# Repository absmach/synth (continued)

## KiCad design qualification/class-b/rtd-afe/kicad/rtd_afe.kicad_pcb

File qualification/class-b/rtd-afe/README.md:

# PT100 4-wire RTD analog front end (SYN-363)

Status: design, placement and a FreeRouting route that is **untrusted and not
release-ready**. The committed evidence is historical (source revision
`01a77d54`); on default settings the export ends `validation_failed` with 12
blocking return-via findings. The board is **not fabricated and not tested on
hardware**. The
SI/PI/RF review is being carried out by the designated reviewer; the automated
evidence and the open items are in [QUALIFICATION.md](QUALIFICATION.md). The
analog accuracy has not been measured, and several sourcing and decoupling items
are open (see Known limits and gaps).

Intended use: a bench or lab 4-wire PT100 front end with a USB readout. It is a
compact mixed-signal board on a single ground plane, not an instrument. Do not
use it for a product or a safety function until the review items in
QUALIFICATION.md are closed.

## What it is

- 4-wire PT100 input on J2 (1x4, 2.54 mm): pin 1 F+, pin 2 S+, pin 3 S-, pin 4
  F-. The force pair carries the excitation current; the sense pair reads the
  element.
- Input filter: R_S1/R_S2 1k 0.1 %, C_D 100 nF X7R across the pair, C_CM1/C_CM2
  10 nF C0G to GND, C_F 10 nF C0G on F+.
- U1 TI ADS124S08 24-bit delta-sigma ADC (VQFN-32, exposed pad) with the
  internal PGA and IDAC1. AIN0 is the force output, AIN1/AIN2 the differential
  sense input. The firmware is expected to select 1 mA excitation.
- U3 TI REF5025AIDR 2.5 V reference on REFP0/REFN0. C_RI and C_RV are 1 uF.
- U2 Raspberry Pi RP2350A (QFN-60), U4 W25Q128JVSIQ QSPI flash (SOIC-8 208 mil, registry `w25q128_flash_208mil`), Y1 ECS-120-20-33-TR
  12 MHz crystal with 33 pF C0G load caps, J3 3-pin SWD header, RUN pull-up.
- J1 USB-C receptacle (HRO TYPE-C-31-M-12), 5.1k CC1/CC2, 27R series on D+/D-,
  D1/D2 SOD-323 TVS on D+/D-. U5 TI LP5907-3.3 LDO (250 mA) makes +3V3 from
  VBUS.
- L2 600 ohm at 100 MHz ferrite bead isolates +3V3A for U1 and U3.
- Four M2.5 non-plated mounting holes at (6, 3.5), (39, 3.5), (6, 40.7) and
  (39, 40.7) mm.
- 40.1 x 44.2 mm rectangular board, 1772 mm², 4 layers, 1.586 mm declared
  stackup (1.6 mm nominal FR4). Board source `rtd_afe.synth`, placement sidecar
  `rtd_afe.placement.layout.toml` (board millimetres). The schematic has no
  sidecar; the compiler lays it out by group.

## Signal chain

J2 -> R_S1/R_S2 and the C_D/C_CM/C_F network -> U1 AIN1/AIN2. The reference is
absolute: VREF = 2.5 V from U3. The current is not used as the reference, so the
IDAC's absolute accuracy and drift limit the measurement unless the firmware
calibrates them. That trade is deliberate and is called out as an open accuracy
item in QUALIFICATION.md.

Nominal filter corners (this work, assuming the 2 k filter resistance dominates
the 100 to 250 ohm PT100):

| Path | Elements | Corner |
| --- | --- | --- |
| Differential | R_S1 + R_S2 = 2 k, C_D 100 nF + C_CM1/C_CM2 in series (5 nF) = 105 nF | about 758 Hz |
| Common mode | R_S 1 k, C_CM 10 nF | about 15.9 kHz |

C_D is ten times each C_CM, so capacitor mismatch turns into little differential
error. C_CM and C_F are C0G; C_D is X7R because no 0603 C0G 100 nF is stocked. The `.synth` notes say "about 720 Hz"; the
difference is only the equivalent capacitance assumed there (110 nF instead of
105 nF). The ADC's digital filter and the chosen output data rate are firmware
settings and are not in this repository.

Excitation and common mode: IDAC1 sources 1 mA into AIN0/F+, through the PT100,
out of F- and through R_BIAS 1k to GND. R_BIAS lifts the RTD common mode to
about 1.0 V plus the RTD drop (about 1.1 V at 100 ohm, 1.25 V at 250 ohm). The
gain-dependent PGA common-mode limit was not re-checked against SBAS660C in this
work; see QUALIFICATION.md.

## Ground

One GND plane on all four copper layers. There is no AGND/DGND split and no tie
resistor. The ADC's AVSS, AVSS_SW, REFN0, REFCOM, exposed pad, DGND pin (14) and
CLK pin (17) return to the same plane as the MCU, flash, USB and LDO. `check.sh`
asserts with pcbnew that the board has `GND` and no `AGND` or `DGND` net. Issue
#363 asked for an AGND/DGND split; the issue owner has not signed off on this
deviation. The return-via advisories on the digital nets are listed in
QUALIFICATION.md for the SI review.

## Placement and routing

Status: routed with FreeRouting 2.4.1 on Java 25, KiCad 10.0.7, Synth at the
worktree this directory was exported from (source revision 01a77d54). The board
was produced with this branch's opt-in fine-pitch return-via relaxation
(`--fine-pitch-return-via-advisory`, needs SI-review sign-off, not given). On
default settings it ends `validation_failed` with 12 blocking return-via
findings, so the board is untrusted and not release-ready (see
QUALIFICATION.md). The route is under review by the designated reviewer.

- Analog left, digital right, packed rather than spread. The input chain is J2
  at (14.8, 41.7) mm, the RC filter just above it and U1 at (12, 25.1) mm. The
  reference and support parts sit in the top-left: U3 at (10.5, 11.6) mm, C_RI
  at (4.8, 11.3) mm, L2 at (13, 6.5) mm, C_RO at (16, 13.6) mm and R_RST at
  (19.8, 14) mm, with R_CC2 at (21, 11.5) mm. The digital core is U2 at
  (28, 29.6) mm, U4 at (22, 19) mm and Y1 at (28, 36.3) mm. U5 is at
  (36.5, 10.5) mm and J3 at (28, 41.7) mm on the bottom edge.
- The outline is fitted to the placement: 40.1 x 44.2 mm, 1772 mm². The largest
  bare rectangle was 7 x 8 mm (56 mm²) on the earlier route (not re-measured after the C_IO, L1 and U4 moves), down from 19 x 19 mm (361 mm²) on the
  50.1 x 44.1 mm rectangle. The board is not a scaled copy: the groups were
  re-packed, so the RTD and AIN lengths changed (RTD_FP 16.78 mm, AIN1
  12.39 mm, AIN2 13.55 mm) and VREF is 37.85 mm of track on F.Cu in the current
  route, still with C_RV at REFP0.
- J2 and J3 are both at y = 41.7 mm; their bodies end about 0.71 mm from the
  bottom edge. J1 is at (22.55, 6.0) mm, centred on the 40.1 mm top edge and
  1.27 mm from it. The extra 1 mm of height over the first compact pass gives
  U2's top-row escapes room; that is what makes the centred connector route
  without an untied GND fragment.
- The sidecar carries a plain rectangular `[[outline]]` (x 2.50..42.59,
  y -0.01..44.21); there is no notch and no post-export cut.
- The RTD/input nets and VREF are on F.Cu only, with no layer change. QSPI is
  mostly on F.Cu, with SD1/SD2 changing layer. SPI_SCK/MOSI/MISO/CS, USB_DN and
  some ADC-control nets change layers; see the SI findings below.
- 389 track segments, 89 vias (60 on GND, 29 signal), 688.4 mm of track. Six of
  the vias are the compact 0.46/0.20 mm size; the rest are 0.6/0.3 mm. 40 nets,
  0 open. The router imported 71 of the vias; the others are not
  router-imported (source stitching and repair vias).
- One via sits inside a pad (C_DV.2, at (16.138, 22.835) mm). `release.json`
  lists it as a fabrication note: order with filled and capped vias.
- `kicad-cli pcb drc --severity-all --refill-zones`: 0 errors, 47 warnings (all `lib_footprint_mismatch`: the exported footprints differ from KiCad 10's library
  copies), 0 unconnected items. `pcbnew.LoadBoard` reopens the board and `check.sh` confirms
  one GND plane with no AGND or DGND net.
- Synth's signal-integrity pass, with the fine-pitch relaxation on (default
  settings: 12 blocking return-via findings): 12 non-blocking findings, 11 `W-SYNTH-DRC-016`
  layer changes with no ground-return via within 0.80 mm (advisories, see
  QUALIFICATION.md) and 1 parallel-run finding (SPI_MISO and ADC_DRDY, 3.5 mm on
  B.Cu, 0.203 mm apart). No RTD, AIN or VREF net is flagged.
- Silkscreen: no DRC warning (the C_DVB label was moved inboard by hand, see `QUALIFICATION.md`). U1 has a hard label override at (16, 30.6) mm;
  29 passives/TVS and H1/H2/H3/J1/J3 have their reference label hidden because
  the compact refdes field has no clear spot. Their refdes remain in the BOM, PnP and
  schematic; the full list is in QUALIFICATION.md.

## Checks

From the repository root:

```
cargo build -p synth-cli
qualification/class-b/rtd-afe/check.sh
```

`check.sh` exports and autoroutes the board into `kicad/`, then runs
`kicad-cli pcb drc --severity-all --refill-zones` and `kicad-cli sch erc` on the
result, renders the 3D views, and loads the board in pcbnew to check that it has
one GND plane. The relaxation is opt-in: `check.sh` passes
`--fine-pitch-return-via-advisory` only when run with
`FINE_PITCH_RETURN_VIA_ADVISORY=1`; the committed evidence was produced with it
on (SI sign-off not given). Without it the script reports the blocking result
and does not replace the evidence. It needs `tools/freerouting/freerouting-2.4.1.jar` and
`tools/jre25/` (both git-excluded; symlink them from a configured Synth
worktree).

Current result:

| Check | Result |
| --- | --- |
| KiCad DRC (errors / warnings / unconnected) | 0 / 47 / 0 |
| pcbnew reopen | OK |
| Ground | one GND plane; no AGND or DGND net |
| KiCad ERC (errors / warnings) | 0 / 1 |
| Synth routing state | routed, 0 open nets |
| Synth release | `production_status: production`, `release_ready: true` (router/export gates only; not a fab approval, see `gate_scope`) |
| Synth SI findings | 12, none blocking (11 `W-SYNTH-DRC-016` advisories, 1 parallel run) |

The ERC warning and all 47 DRC warnings are library-comparison warnings,
not connectivity errors. The embedded REF5025ID symbol differs from the installed
library copy. The 47 are `lib_footprint_mismatch`: Synth's exporter
now redraws each footprint's reference label at 0.8 mm with an 0.18 mm stroke
and trims silkscreen that would clip a pad or via, so the embedded footprint
differs from the `Resistor_SMD`/`Capacitor_SMD` library copy. No copper, pad or
drill is changed. The exported schematic embeds its own symbols and the
netlist/PCB parity is clean. This disposition has not been reviewed by a human.

## Committed artifacts

- `kicad/`: routed PCB, schematic, symbol library, project, DRC rules, BOM, PnP,
  Gerbers and drill files.
- `reports/`: `release.json`, the delivered DRC and ERC reports, the KiCad
  netlist, the FreeRouting routing record and the connectivity report.
- `images/`: 3D top, bottom and angled views and the schematic. The 3D views
  are rendered with `kicad-cli pcb render`, the schematic with
  `kicad-cli sch export pdf` and `pdftoppm`.
- `kicad/rtd_afe.step`: board STEP with 3D models, exported by `kicad-cli pcb export step --no-dnp`; the 3D views use the same models. Stock KiCad models, except the ADS124S08 and RP2350, which use the simplified models in `agent-run/step-models/` (from datasheet dimensions, not vendor CAD), and the USB-C receptacle, which uses the GrabCAD model in `../models/` (see its README for source and offset). The STEP and the 3D images are made from a scratch copy of the board that names these models; the committed `kicad_pcb` still names KiCad's library path for the USB-C file, because the exporter has no custom-model path yet. The mounting holes have no model (the KiCad MountingHole step files are not installed).
- `rtd_afe.synth`, `rtd_afe.placement.layout.toml`: the design sources.
- `check.sh`: the acceptance check above.
- `SHA256SUMS`: hashes of the artifacts.

The committed `kicad/`, `reports/`, `images/` and `SHA256SUMS` are historical output from source revision 01a77d54; the current tree does not route, so they are not reproducible from head (see QUALIFICATION.md, Reproducibility). `reports/release.json` (production, `release_ready: true`, reviewers all `reviewed`) is generated output from that revision and does not reflect the PR status (untrusted, `release_ready: false`, crystal unreviewed). `kicad/bom.csv` is historical and predates the source pins (C_D, L1, Y1).

The reports are as the commands produce them, except that `check.sh` rewrites
the checkout path in `release.json`, `rtd_afe.routing.json` and `rtd_afe.net` to
a repository-relative one and stamps `source_revision` from the checked-out
commit. `release.json` is Synth's own format (`synth.release.v1`); its
`gate_scope` says it is a router/DRC gate, not a fabrication approval or a
component review.

## Known limits and gaps

- No VBUS fuse, TVS or reverse-polarity protection. D1/D2 protect only D+/D-.
  CC1/CC2 have no TVS. The USB shield is tied directly to GND.
- D1/D2 are pinned to ESD5V0B03-323 (LCSC C521915) in the source; the registry
  part is generic and the BOM's `ESD` value text is a placeholder.
- The BOM carries `dielectric`, `voltage`, `tolerance` and `power` columns from
  the source, so the C0G filter caps and the 0.1 % resistors are visible to an
  assembler. Empty cells mean the source does not declare that attribute.
- The source declares `requires via_in_pad` and the manufacturer profile
  `jlc-filled-via`. This route has one via inside a pad (C_DV.2), listed in
  `release.json` as a fabrication note. JLCPCB has not accepted that process.
- There are no test points. The 12-pad set (rails, reference, USB and SWD) was
  tried on the earlier outline; every routing attempt left GND islands. The
  top-left area it used now holds the reference cluster.
- No VBUS current budget was measured. The LDO is 250 mA; the RP2350 datasheet
  peak plus the ADC, reference and flash is expected to be below it, but this
  was not checked against the loads.
- The reference is absolute, not ratiometric. IDAC accuracy and drift therefore
  enter the result; no calibration or IDAC accuracy check was done.
- The unused ADC analog inputs (AIN3..AIN11, AINCOM), REFP1/REFN1, the ADC GPIOs
  and pin 25 are left open. Their termination is not covered by a datasheet
  review here.
- The firmware does not exist in this repository: gain, data rate, IDAC value,
  register map, USB descriptors and calibration are all unwritten/untested.
- Synth has no free-text silkscreen primitive, so the board name and revision
  are not on the copper. Header pin functions are not labelled on the silk.
- The board is 40.1 x 44.2 mm (1772 mm²), down from the 50.1 x 44.1 mm
  rectangle and the earlier 63.1 x 51.1 mm. The floorplan packs the analog chain
  and reference at the left and the MCU/flash/crystal and USB at the right, with
  the groups interlocking vertically instead of sitting in two sparse columns.
  It is one successful FreeRouting run, not a proven densest layout.
- The sidecar carries a plain rectangular `[[outline]]`, not a notch; the
  exporter reproduces it without a post-export cut.
- 29 passives/TVS and H1/H2/H3/J1/J3 have their reference label hidden because
  the refdes field has no clear spot in the compact layout. The refdes are still in
  the BOM, PnP and schematic; the full list is in QUALIFICATION.md.
- RP2350 decoupling is below the recommendation. The board has four IOVDD 100 nF
  caps (C_IO1..C_IO4) for six IOVDD pins, and two DVDD caps (C_DV1, C_DV2) plus
  C_DVB bulk for three DVDD pins. Raspberry Pi's hardware design guide (section
  2.2.1) recommends one 100 nF per power pin, with pins 53/54 sharing one. Four
  more caps could not be placed without breaking routing; left for the SI/PI
  review.
- L1 is pinned to Sunlord MPL2012S3R3MHT (C98331, 0805); its DCR and saturation current are not checked against the RP2350 datasheet. The Pi-recommended Abracon AOTA-B201610S3R3-101-T (C42411119) does not fit the 0805 footprint.
- C_D is X7R 0603 (C14663), not C0G: no 0603 C0G 100 nF is stocked. A 1206 C0G part (C170182) broke routing and was reverted.
- Y1 is pinned to C2449814 (exact MPN).
- Issue #363 asked for an AGND/DGND split; this board uses one GND plane and the
  issue owner has not signed off on the deviation.
- No GitHub issue numbers are linked for the Synth defects listed in
  QUALIFICATION.md.
- The mounting holes leave 2.15 to 2.24 mm of material around a 2.7 mm hole, the ISO 273 fine clearance for M2.5.
  J2/J3 are about 0.71 mm from the bottom edge and J1 1.27 mm from the top.
  The enclosure and screw-head clearance are mechanical check items; the
  measured table is in QUALIFICATION.md.
- The KiCad ERC library-name warnings remain (see above). They do not affect
  the netlist.

## Not verified

- Analog accuracy, noise, linearity, drift and the actual PT100 reading.
- The IDAC absolute accuracy/drift, PGA common-mode range at the chosen gain,
  the ADC's unused-input termination, and the RC filter against the chosen ADC
  data rate.
- The 1.1 V core regulator, the 12 MHz crystal's ESR/drive level, the flash
  QSPI timing, and the USB full-speed signal integrity.
- ESD, surge, reverse polarity and USB-C compliance.
- Mechanical fit, connector and header orientation, mounting-hole clearance.
- Any fabrication or assembly check. Nothing was sent to a fab house.
- Any part was bought or measured. Part-level registry reviews exist (see
  QUALIFICATION.md); the HRO and Tech Public datasheets were read as scans.

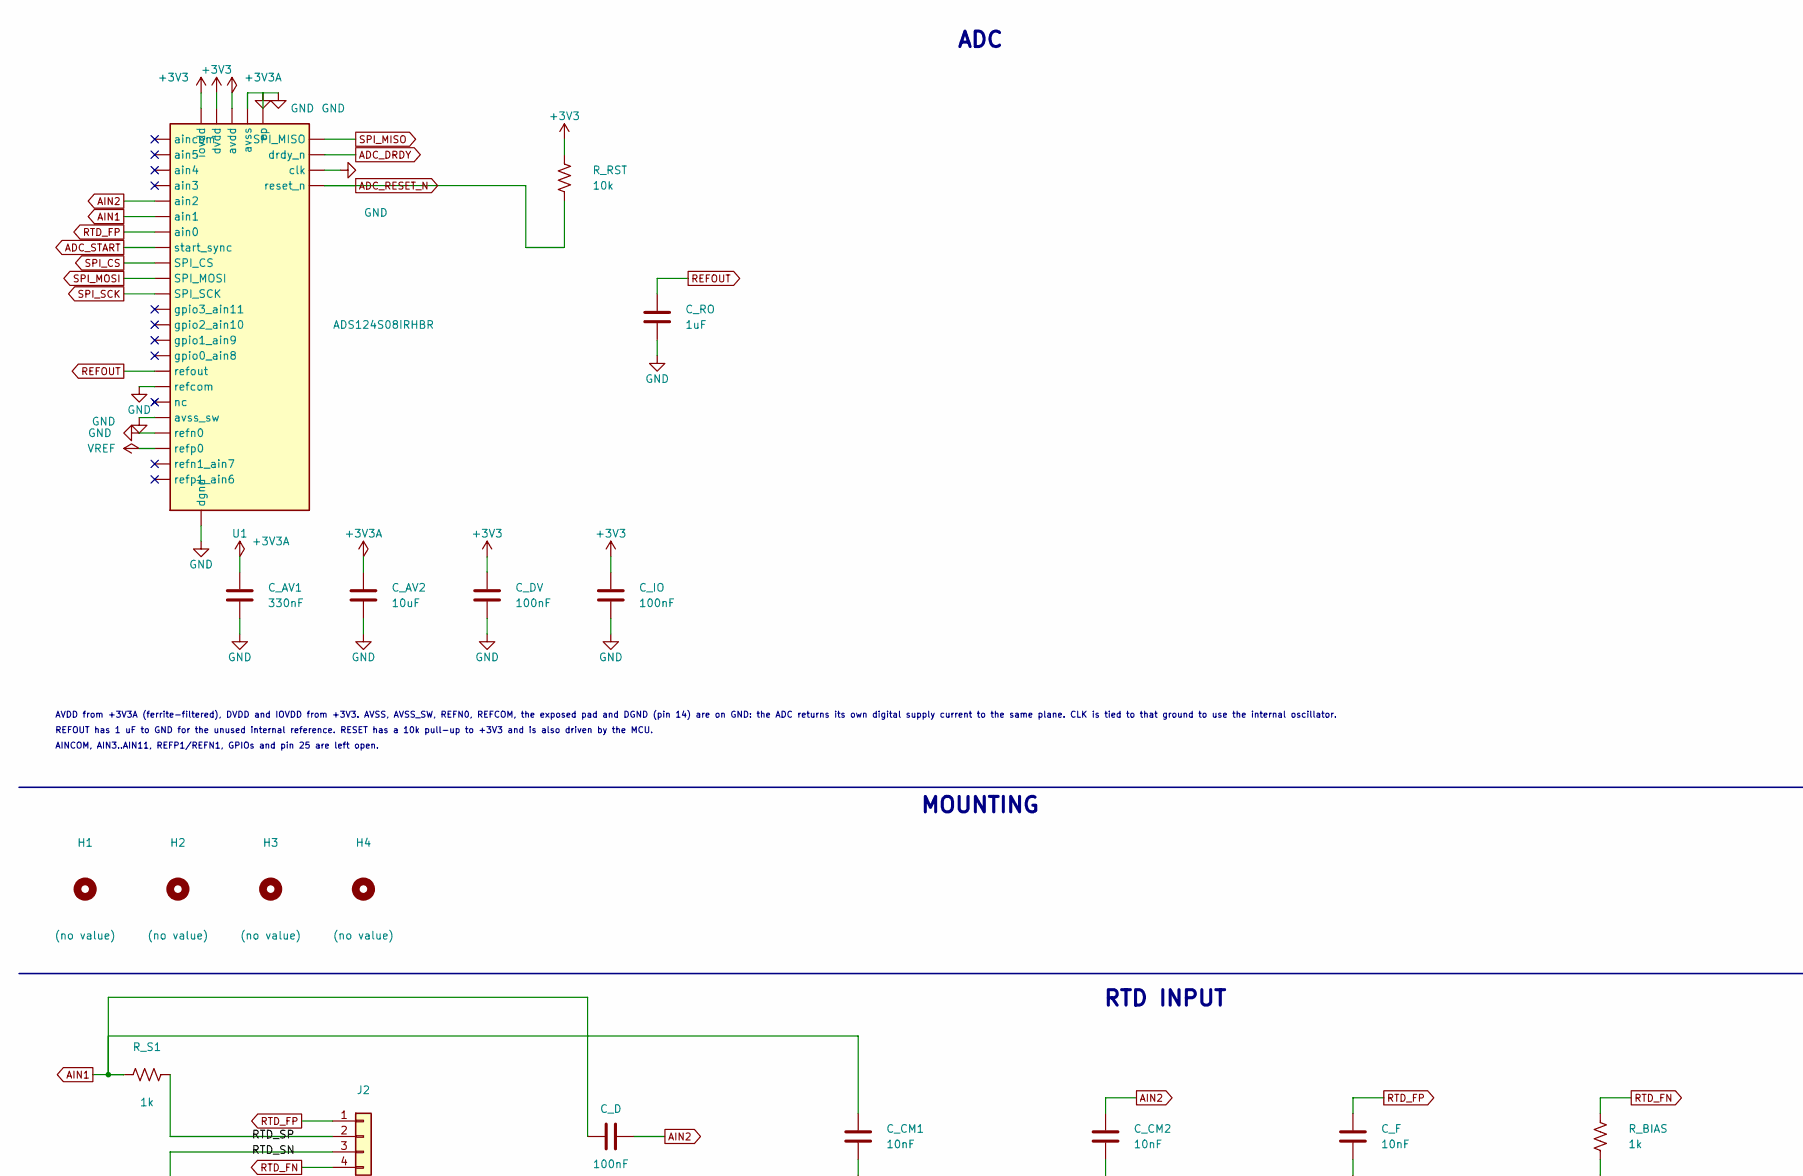
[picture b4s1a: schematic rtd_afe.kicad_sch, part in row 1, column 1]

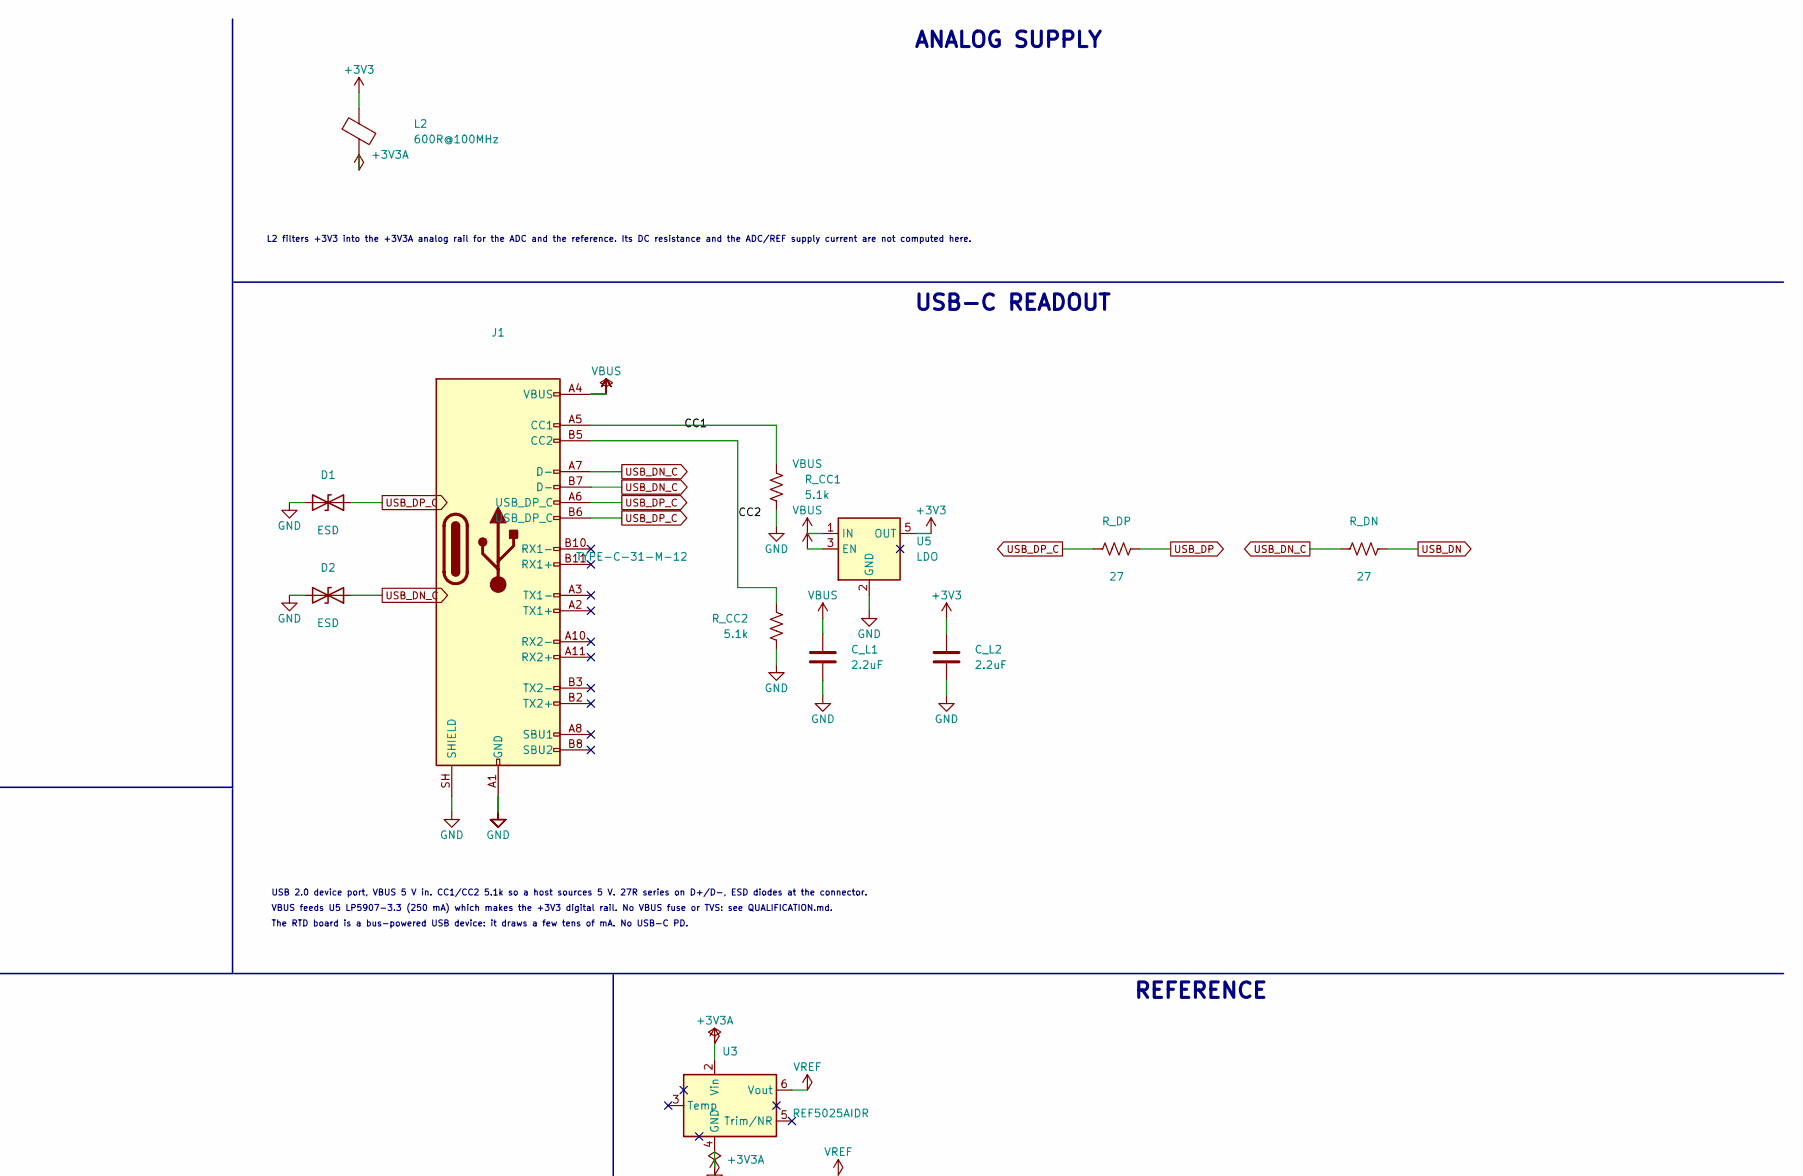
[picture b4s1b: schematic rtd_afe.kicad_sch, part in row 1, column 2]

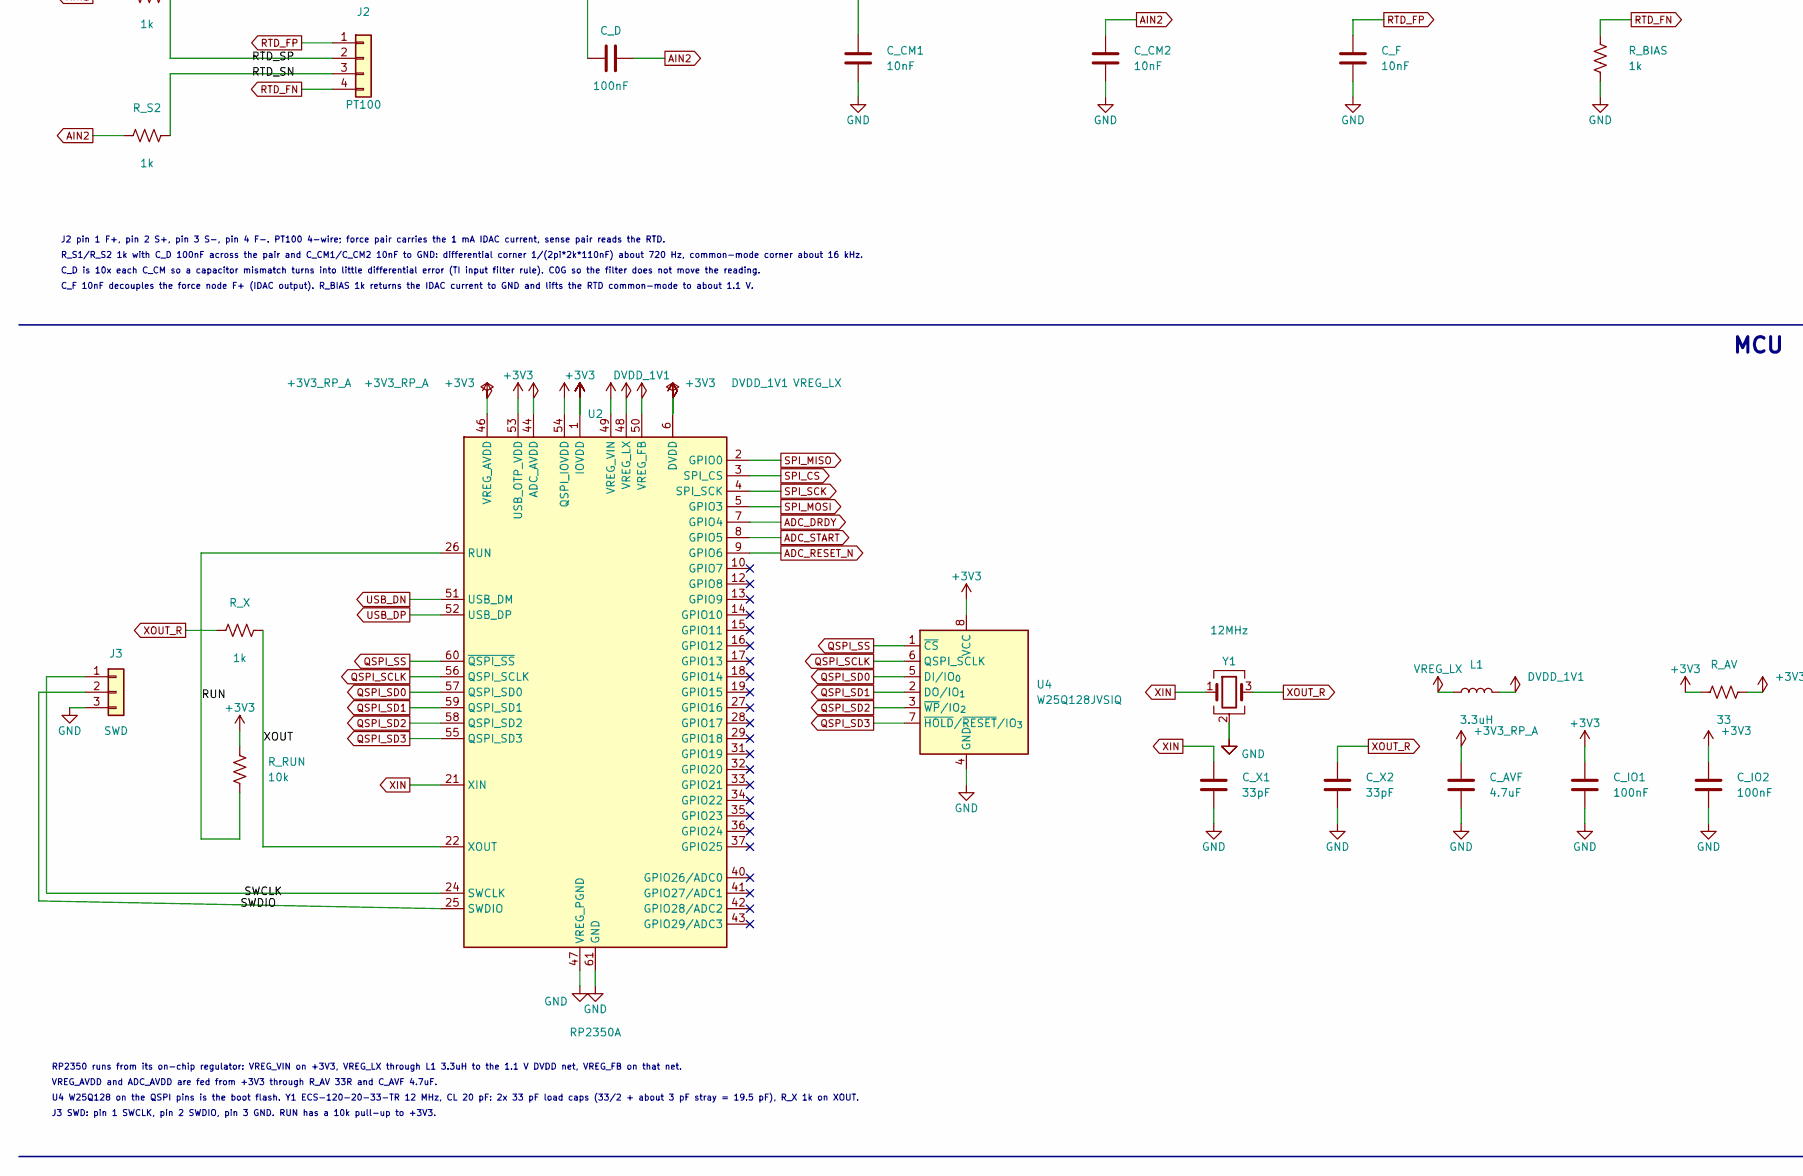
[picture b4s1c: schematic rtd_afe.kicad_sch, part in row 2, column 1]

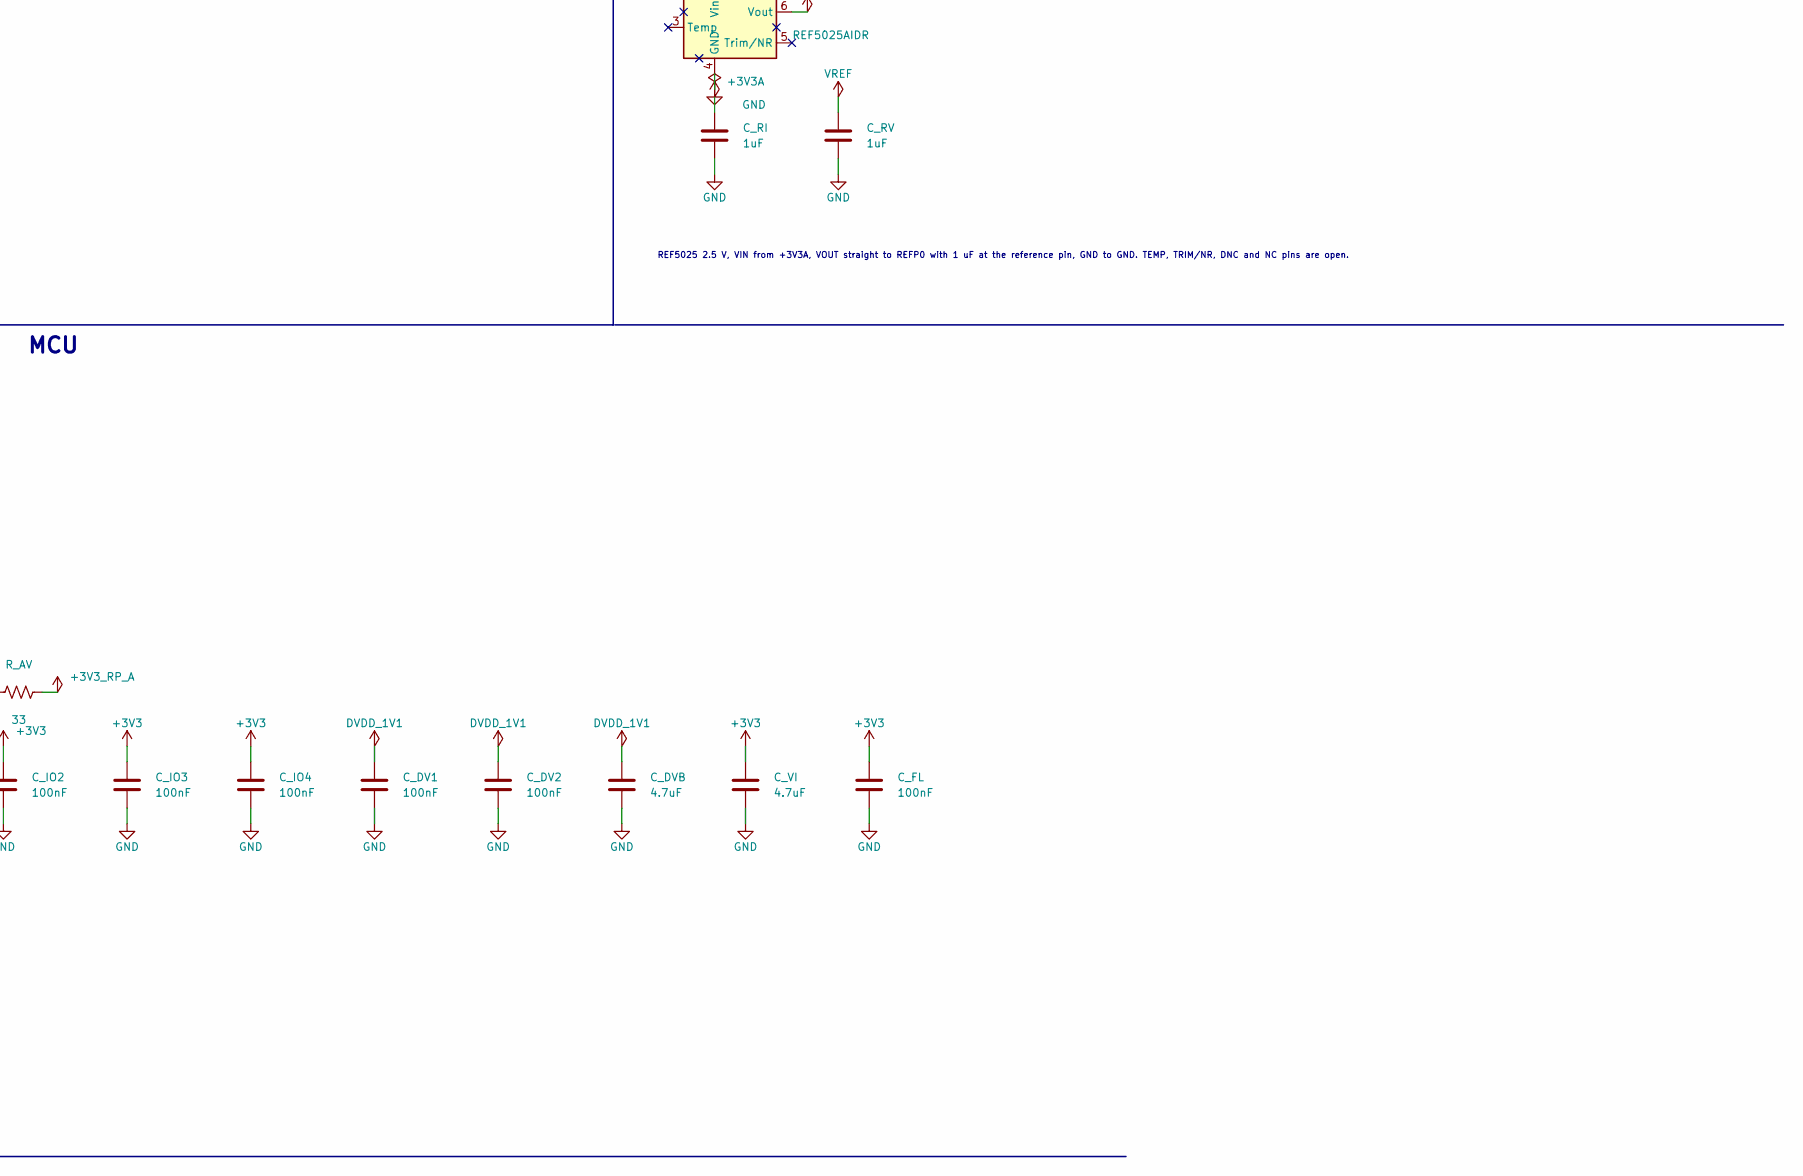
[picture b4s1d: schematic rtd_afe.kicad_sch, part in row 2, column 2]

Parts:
C_AV1: 330nF; C_0603_1608Metric; Voltage 10V; MPN 0603B334K500NT; LCSC C188679
C_AV2: 10uF; C_0805_2012Metric; Voltage 10V; MPN TCC0805X7R106K160FT; LCSC C380347
C_AVF: 4.7uF; C_0603_1608Metric; Voltage 10V; MPN TCC0603X7R475K100CT; LCSC C18185770
C_CM1, C_CM2: 10nF; C_0603_1608Metric; Voltage 50V; MPN 0603N103J500CT; LCSC C2894187
C_D: 100nF; C_0603_1608Metric; Voltage 50V
C_DV, C_DV1, C_DV2: 100nF; C_0603_1608Metric; Voltage 10V; MPN CC0603KRX7R9BB104; LCSC C14663
C_DVB: 4.7uF; C_0805_2012Metric; Voltage 10V; MPN CC0805KKX7R8BB475; LCSC C354262
C_F: 10nF; C_0603_1608Metric; Voltage 50V; MPN 0603N103J500CT; LCSC C2894187
C_FL: 100nF; C_0603_1608Metric; Voltage 10V; MPN CC0603KRX7R9BB104; LCSC C14663
C_IO, C_IO1, C_IO2, C_IO3, C_IO4: 100nF; C_0603_1608Metric; Voltage 10V; MPN CC0603KRX7R9BB104; LCSC C14663
C_L1, C_L2: 2.2uF; C_0603_1608Metric; Voltage 16V; MPN 0603B225K160NT; LCSC C43922
C_RI: 1uF; C_0603_1608Metric; Voltage 10V; MPN 0603B105K160NT; LCSC C93816
C_RO: 1uF; C_0603_1608Metric; Voltage 10V; MPN 0603B105K160NT; LCSC C93816
C_RV: 1uF; C_0603_1608Metric; Voltage 10V; MPN 0603B105K160NT; LCSC C93816
C_VI: 4.7uF; C_0603_1608Metric; Voltage 10V; MPN TCC0603X7R475K100CT; LCSC C18185770
C_X1, C_X2: 33pF; C_0603_1608Metric; Voltage 50V; MPN CL10C330JB8NNNC; LCSC C1663
D1, D2: ESD; D_SOD-323; MPN ESD5V0B03-323; LCSC C521915
H1, H2, H3, H4: (no value); MountingHole_2.5mm
J1: TYPE-C-31-M-12; USB_C_Receptacle_HRO_TYPE-C-31-M-12; MPN TYPE-C-31-M-12; LCSC C165948
J2: PT100; PinHeader_1x04_P2.54mm_Vertical; MPN PZ254V-11-04P; LCSC C492403
J3: SWD; PinHeader_1x03_P2.54mm_Vertical; MPN PZ254V-11-03P; LCSC C2937625
L1: 3.3uH; L_0805_2012Metric
L2: 600R@100MHz; L_0603_1608Metric; MPN BLM18AG601SN1D; LCSC C19330
R_AV: 33; R_0603_1608Metric; MPN FRC0603F33R0TS; LCSC C2909394
R_BIAS: 1k; R_0603_1608Metric; Tolerance 0.1%; MPN RT0603BRD071KL; LCSC C110776
R_CC1, R_CC2: 5.1k; R_0603_1608Metric; MPN 0603WAF5101T5E; LCSC C23186
R_DN: 27; R_0603_1608Metric; MPN 0603WAF270JT5E; LCSC C25190
R_DP: 27; R_0603_1608Metric; MPN 0603WAF270JT5E; LCSC C25190
R_RST: 10k; R_0603_1608Metric; MPN 0603WAF1002T5E; LCSC C25804
R_RUN: 10k; R_0603_1608Metric; MPN 0603WAF1002T5E; LCSC C25804
R_S1, R_S2: 1k; R_0603_1608Metric; Tolerance 0.1%; MPN RT0603BRD071KL; LCSC C110776
R_X: 1k; R_0603_1608Metric; MPN 0603WAF1001T5E; LCSC C21190
U1: ADS124S08IRHBR; Texas_RHB0032M_VQFN-32-1EP_5x5mm_P0.5mm_EP2.1x2.1mm; MPN ADS124S08IRHBR
U2: RP2350A; QFN-60-1EP_7x7mm_P0.4mm_EP3.4x3.4mm; MPN RP2350A; LCSC C14663
U3: REF5025AIDR; SOIC-8_3.9x4.9mm_P1.27mm; MPN REF5025AIDR
U4: W25Q128JVSIQ; SOIC-8_3.9x4.9mm_P1.27mm; MPN W25Q128JVSIQ; LCSC C97521
U5: LDO; SOT-23-5; MPN LP5907MFX-3.3/NOPB; LCSC C80670
Y1: 12MHz; Crystal_SMD_3225-4Pin_3.2x2.5mm; MPN ECS-120-20-33-TR

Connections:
+3V3: C_DV.1, C_FL.1, C_IO.1, C_IO1.1, C_IO2.1, C_IO3.1, C_IO4.1, C_L2.1, C_VI.1, L2.1, R_AV.1, R_RST.1, R_RUN.1, U1.15 (iovdd), U1.16 (dvdd), U2.1 (IOVDD), U2.11 (IOVDD), U2.20 (IOVDD), U2.30 (IOVDD), U2.38 (IOVDD), U2.45 (IOVDD), U2.49 (VREG_VIN), U2.53 (USB_OTP_VDD), U2.54 (QSPI_IOVDD), U4.8 (VCC), U5.5 (OUT)
+3V3A: C_AV1.1, C_AV2.1, C_RI.1, L2.2, U1.26 (avdd), U3.2 (Vin)
+3V3_RP_A: C_AVF.1, R_AV.2, U2.44 (ADC_AVDD), U2.46 (VREG_AVDD)
ADC_DRDY: U1.13 (drdy_n), U2.7 (GPIO4)
ADC_RESET_N: R_RST.2, U1.18 (reset_n), U2.9 (GPIO6)
ADC_START: U1.8 (start_sync), U2.8 (GPIO5)
AIN1: C_CM1.1, C_D.1, R_S1.2, U1.6 (ain1)
AIN2: C_CM2.1, C_D.2, R_S2.2, U1.5 (ain2)
CC1: J1.A5 (CC1), R_CC1.1
CC2: J1.B5 (CC2), R_CC2.1
DVDD_1V1: C_DV1.1, C_DV2.1, C_DVB.1, L1.2, U2.6 (DVDD), U2.23 (DVDD), U2.39 (DVDD), U2.50 (VREG_FB)
GND: C_AV1.2, C_AV2.2, C_AVF.2, C_CM1.2, C_CM2.2, C_DV.2, C_DV1.2, C_DV2.2, C_DVB.2, C_F.2, C_FL.2, C_IO.2, C_IO1.2, C_IO2.2, C_IO3.2, C_IO4.2, C_L1.2, C_L2.2, C_RI.2, C_RO.2, C_RV.2, C_VI.2, C_X1.2, C_X2.2, D1.2 (A2), D2.2 (A2), J1.A1 (GND), J1.A12 (GND), J1.B1 (GND), J1.B12 (GND), J1.SH (SHIELD), J3.3, R_BIAS.2, R_CC1.2, R_CC2.2, U1.14 (dgnd), U1.17 (clk), U1.24 (refcom), U1.27 (avss), U1.28 (avss_sw), U1.29 (refn0), U1.33 (ep), U2.47 (VREG_PGND), U2.61 (GND), U3.4 (GND), U4.4 (GND), U5.2 (GND), Y1.2 (G), Y1.4 (G)
QSPI_SCLK: U2.56 (QSPI_SCLK), U4.6 (CLK)
QSPI_SD0: U2.57 (QSPI_SD0), U4.5 (DI/IO_{0})
QSPI_SD1: U2.59 (QSPI_SD1), U4.2 (DO/IO_{1})
QSPI_SD2: U2.58 (QSPI_SD2), U4.3 (~WP/IO_{2})
QSPI_SD3: U2.55 (QSPI_SD3), U4.7 (~HOLD/~RESET/IO_{3})
QSPI_SS: U2.60 (~QSPI_SS), U4.1 (~CS)
REFOUT: C_RO.1, U1.23 (refout)
RTD_FN: J2.4, R_BIAS.1
RTD_FP: C_F.1, J2.1, U1.7 (ain0)
RTD_SN: J2.3, R_S2.1
RTD_SP: J2.2, R_S1.1
RUN: R_RUN.2, U2.26 (RUN)
SPI_CS: U1.9 (cs_n), U2.3 (GPIO1)
SPI_MISO: U1.12 (dout_drdy), U2.2 (GPIO0)
SPI_MOSI: U1.10 (din), U2.5 (GPIO3)
SPI_SCK: U1.11 (sclk), U2.4 (GPIO2)
SWCLK: J3.1, U2.24 (SWCLK)
SWDIO: J3.2, U2.25 (SWDIO)
USB_DN: R_DN.2, U2.51 (USB_DM)
USB_DN_C: D2.1 (A1), J1.A7 (D-), J1.B7 (D-), R_DN.1
USB_DP: R_DP.2, U2.52 (USB_DP)
USB_DP_C: D1.1 (A1), J1.A6 (D+), J1.B6 (D+), R_DP.1
VBUS: C_L1.1, J1.A4 (VBUS), J1.A9 (VBUS), J1.B4 (VBUS), J1.B9 (VBUS), U5.1 (IN), U5.3 (EN)
VREF: C_RV.1, U1.30 (refp0), U3.6 (Vout)
VREG_LX: L1.1, U2.48 (VREG_LX)
XIN: C_X1.1, U2.21 (XIN), Y1.1
XOUT: R_X.1, U2.22 (XOUT)
XOUT_R: C_X2.1, R_X.2, Y1.3

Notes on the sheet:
MOUNTING
RTD INPUT
ADC
REFERENCE
ANALOG SUPPLY
MCU
USB-C READOUT
J2 pin 1 F+, pin 2 S+, pin 3 S-, pin 4 F-. PT100 4-wire; force pair carries the 1 mA IDAC current, sense pair reads the RTD.
R_S1/R_S2 1k with C_D 100nF across the pair and C_CM1/C_CM2 10nF to GND: differential corner 1/(2pi*2k*110nF) about 720 Hz, common-mode corner about 16 kHz.
C_D is 10x each C_CM so a capacitor mismatch turns into little differential error (TI input filter rule). C0G so the filter does not move the reading.
C_F 10nF decouples the force node F+ (IDAC output). R_BIAS 1k returns the IDAC current to GND and lifts the RTD common-mode to about 1.1 V.
AVDD from +3V3A (ferrite-filtered), DVDD and IOVDD from +3V3. AVSS, AVSS_SW, REFN0, REFCOM, the exposed pad and DGND (pin 14) are on GND: the ADC returns its own digital supply current to the same plane. CLK is tied to that ground to use the internal oscillator.
REFOUT has 1 uF to GND for the unused internal reference. RESET has a 10k pull-up to +3V3 and is also driven by the MCU.
AINCOM, AIN3..AIN11, REFP1/REFN1, GPIOs and pin 25 are left open.
REF5025 2.5 V, VIN from +3V3A, VOUT straight to REFP0 with 1 uF at the reference pin, GND to GND. TEMP, TRIM/NR, DNC and NC pins are open.
L2 filters +3V3 into the +3V3A analog rail for the ADC and the reference. Its DC resistance and the ADC/REF supply current are not computed here.
RP2350 runs from its on-chip regulator: VREG_VIN on +3V3, VREG_LX through L1 3.3uH to the 1.1 V DVDD net, VREG_FB on that net.
VREG_AVDD and ADC_AVDD are fed from +3V3 through R_AV 33R and C_AVF 4.7uF.
U4 W25Q128 on the QSPI pins is the boot flash. Y1 ECS-120-20-33-TR 12 MHz, CL 20 pF: 2x 33 pF load caps (33/2 + about 3 pF stray = 19.5 pF), R_X 1k on XOUT.
J3 SWD: pin 1 SWCLK, pin 2 SWDIO, pin 3 GND. RUN has a 10k pull-up to +3V3.
USB 2.0 device port, VBUS 5 V in. CC1/CC2 5.1k so a host sources 5 V. 27R series on D+/D-, ESD diodes at the connector.
VBUS feeds U5 LP5907-3.3 (250 mA) which makes the +3V3 digital rail. No VBUS fuse or TVS: see QUALIFICATION.md.
The RTD board is a bus-powered USB device: it draws a few tens of mA. No USB-C PD.

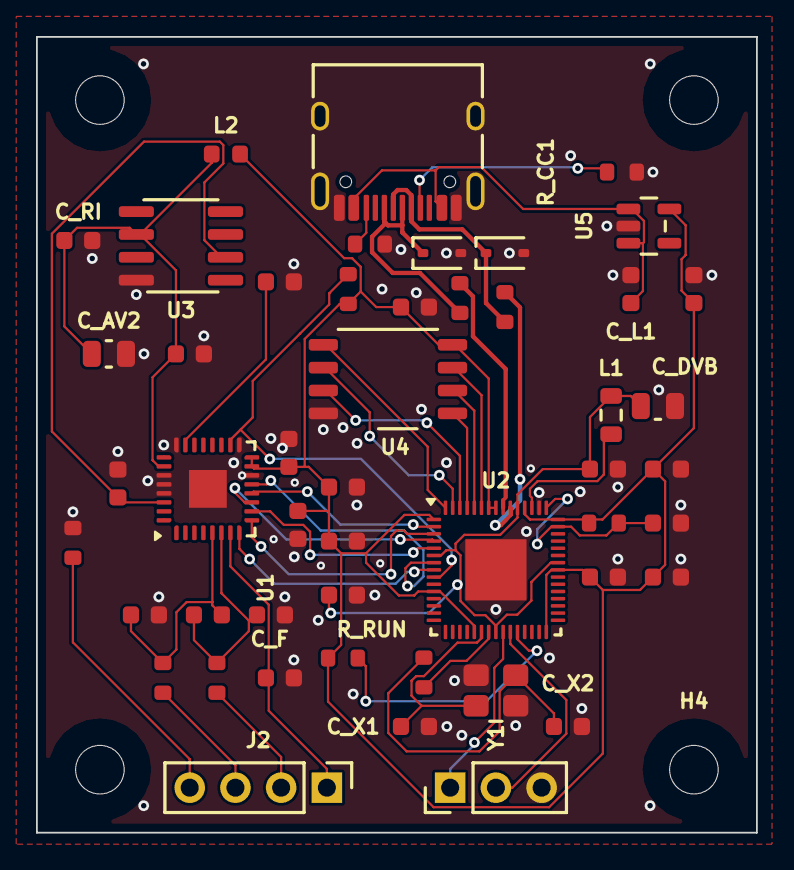
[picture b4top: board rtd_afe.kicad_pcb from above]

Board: 4 copper layers, 40.0 x 44.2 mm, 53 parts (0 on the bottom side), 40 nets.
